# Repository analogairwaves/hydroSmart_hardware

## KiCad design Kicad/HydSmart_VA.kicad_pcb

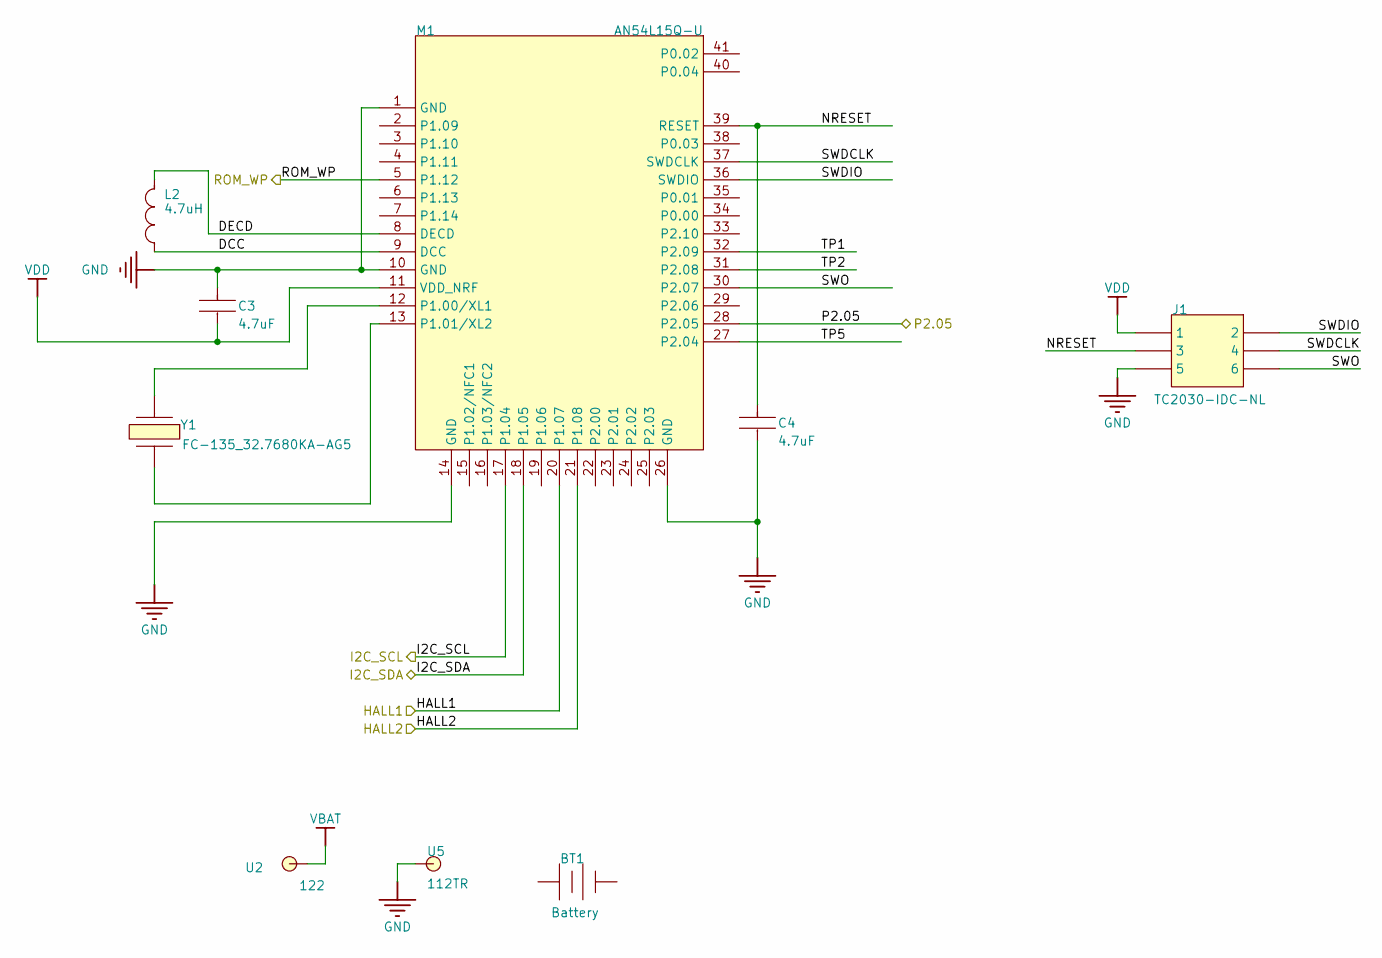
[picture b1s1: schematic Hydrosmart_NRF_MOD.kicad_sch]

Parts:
BT1: Battery; BAT-2; MANUFACTURER_PART_NUMBER CR2477
C3: 4.7uF; C0402; VOLTAGE RATING 16V; MANUFACTURER_PART_NUMBER GRM155D81C475ME15J
C4: 4.7uF; C0402; VOLTAGE RATING 16V; TOLERANCE 20%; MANUFACTURER_PART_NUMBER GRM155D81C475ME15J
J1: TC2030-IDC-NL
L2: 4.7uH; FP-MLZ1608-IPC_A; CURRENT RATING 350mA; TOLERANCE 20%; MANUFACTURER_PART_NUMBER MLZ1608E4R7MT000
M1: AN54L15Q-U; MANUFACTURER_PART_NUMBER AN54L15Q-U
U2: 122; MANUFACTURER_PART_NUMBER 122
U5: 112TR; MANUFACTURER_PART_NUMBER 112TR
Y1: FC-135_32.7680KA-AG5; FC135327680KAAG5; MANUFACTURER_PART_NUMBER FC-135 32.7680KA-AG5; MOUSER PART NUMBER 732-532.7680KA-AG5

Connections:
/HALL1: M1.20 (P1.07); also elsewhere on the board
/HALL2: M1.21 (P1.08); also elsewhere on the board
/Hydrosmart_NRF_MOD/DCC: L2.2, M1.9 (DCC)
/Hydrosmart_NRF_MOD/DECD: L2.1, M1.8 (DECD)
/Hydrosmart_NRF_MOD/NRESET: C4.1, J1.3, M1.39 (RESET)
/Hydrosmart_NRF_MOD/SWDCLK: J1.4, M1.37 (SWDCLK)
/Hydrosmart_NRF_MOD/SWDIO: J1.2, M1.36 (SWDIO)
/Hydrosmart_NRF_MOD/SWO: J1.6, M1.30 (P2.07)
/Hydrosmart_NRF_MOD/TP1: M1.32 (P2.09)
/Hydrosmart_NRF_MOD/TP2: M1.31 (P2.08)
/Hydrosmart_NRF_MOD/TP5: M1.27 (P2.04)
/I2C_SCL: M1.17 (P1.04); also elsewhere on the board
/I2C_SDA: M1.18 (P1.05); also elsewhere on the board
/P2.05: M1.28 (P2.05); also elsewhere on the board
/ROM_WP: M1.5 (P1.12); also elsewhere on the board
GND: C3.1, C4.2, J1.5, M1.1 (GND), M1.10 (GND), M1.14 (GND), M1.26 (GND), U5.1; also elsewhere on the board
unnamed: M1.12 (P1.00/XL1), Y1.1
unnamed: M1.13 (P1.01/XL2), Y1.2 (CRYSTAL_2)
VBAT: U2.1; also elsewhere on the board
VDD: C3.2, J1.1, M1.11 (VDD_NRF); also elsewhere on the board

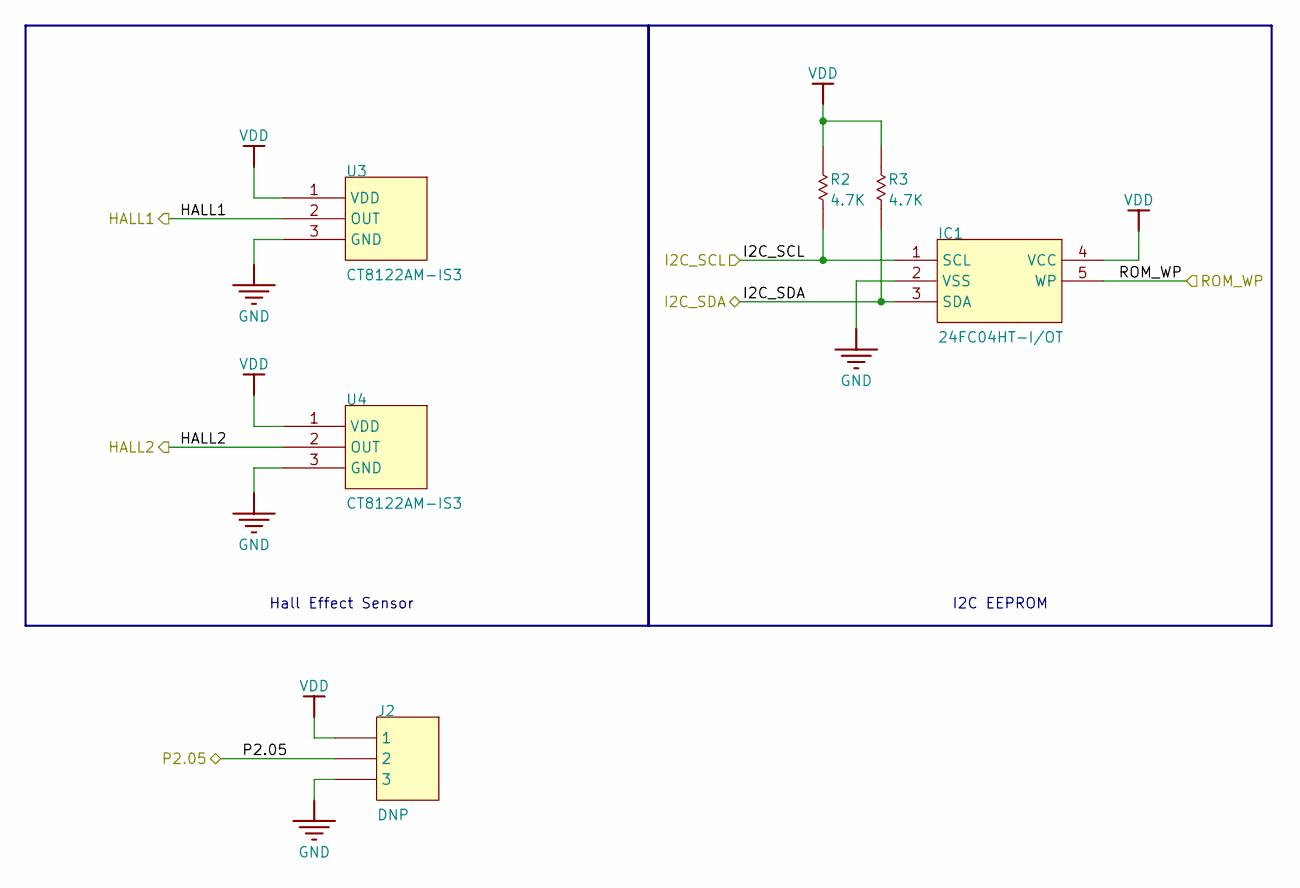
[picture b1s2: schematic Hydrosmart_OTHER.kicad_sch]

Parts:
IC1: 24FC04HT-I/OT; SOT23-5; MANUFACTURER_PART_NUMBER 24FC04HT-I/OT; DIGIKEY PART NUMBER 24FC04HT-I/OTCT-ND
J2: DNP; HDR1X3
R2, R3: 4.7K; R0402; MANUFACTURER_PART_NUMBER ERJ-2RKF4701X
U3, U4: CT8122AM-IS3; SOT95P280X135-3L; MANUFACTURER_PART_NUMBER CT8122AM-IS3

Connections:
/HALL1: U3.2 (OUT); also elsewhere on the board
/HALL2: U4.2 (OUT); also elsewhere on the board
/I2C_SCL: IC1.1 (SCL), R2.1; also elsewhere on the board
/I2C_SDA: IC1.3 (SDA), R3.1; also elsewhere on the board
/P2.05: J2.2; also elsewhere on the board
/ROM_WP: IC1.5 (WP); also elsewhere on the board
GND: IC1.2 (VSS), J2.3, U3.3 (GND), U4.3 (GND); also elsewhere on the board
VDD: IC1.4 (VCC), J2.1, R2.2, R3.2, U3.1 (VDD), U4.1 (VDD); also elsewhere on the board

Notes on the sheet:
I2C EEPROM
Hall Effect Sensor

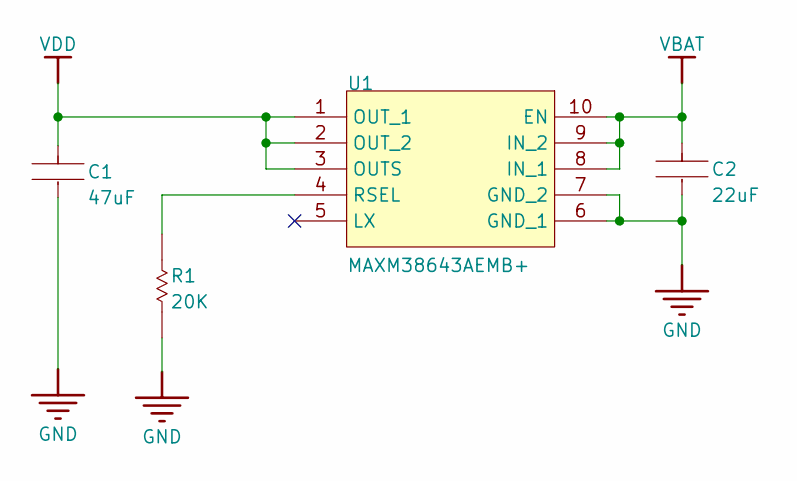
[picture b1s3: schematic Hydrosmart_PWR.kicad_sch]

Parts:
C1: 47uF; FP-C2012-125-0_2-MFG; TOLERANCE 20%; VOLTAGE RATING 6.3V; MANUFACTURER_PART_NUMBER JMK212BBJ476MG-T
C2: 22uF; FP-GRM158-0_2-MFG; MANUFACTURER_PART_NUMBER GRM158R60J226ME01D
R1: 20K; R0402; MANUFACTURER_PART_NUMBER ERJ-2RKF2002X
U1: MAXM38643AEMB+; MAXM38643AEMB; MANUFACTURER_PART_NUMBER MAXM38643AEMB+; MOUSER PART NUMBER 700-MAXM38643AEMB+

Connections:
GND: C1.2, C2.2, R1.1, U1.6 (GND_1), U1.7 (GND_2); also elsewhere on the board
unnamed: R1.2, U1.4 (RSEL)
VBAT: C2.1, U1.8 (IN_1), U1.9 (IN_2), U1.10 (EN); also elsewhere on the board
VDD: C1.1, U1.1 (OUT_1), U1.2 (OUT_2), U1.3 (OUTS); also elsewhere on the board

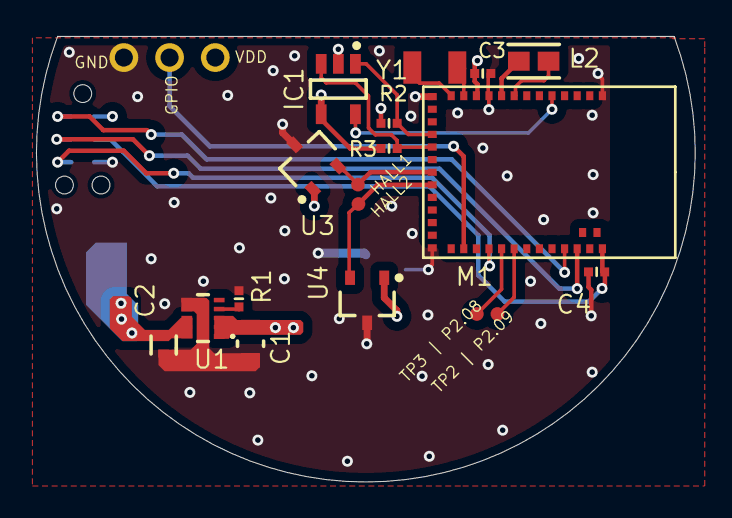
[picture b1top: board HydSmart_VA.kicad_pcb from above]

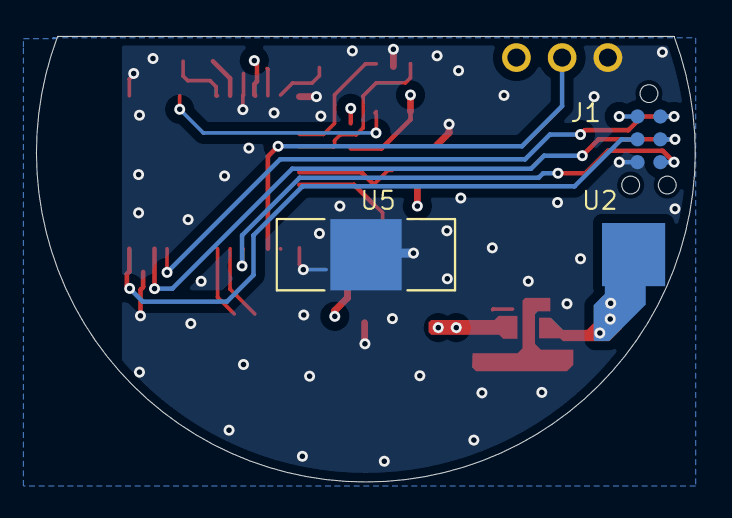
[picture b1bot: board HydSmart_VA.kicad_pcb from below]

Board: 4 copper layers, 36.6 x 24.8 mm, 18 parts (3 on the bottom side), 18 nets.

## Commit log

2025-06-27 VA released initial commit
2025-06-27 Checked, updated design
    + Checked, updated information related to BOM.
    + Updated PCB.
    + Generated manufacturing files.
2025-06-30 + Updated design based on new notes
2025-06-30 + Added 3D model
2025-07-01 - Updated information related to BOM
2025-07-02 + Updated design based on new notes, generated manufacturing files and 3D model
2025-07-02 + Fixed 3D model, moved U2 label
2025-07-02 + Updated schematic
2025-07-02 + Added pull up resistors for I2C signals
2025-07-02 + Moved programming pads to back side
2025-07-09 assembly diagrams added
2025-07-13 + Fixed issue on U2 and U5, added battery to the schematic and BOM
2025-07-23 assembly pictures added
2025-09-03 + Converted design to Kicad, exported 3D model
2025-09-04 + Created library and added information related to BOM: MANUFACTURER and MANUFACTURER PN
2025-09-12 VB changes start. Updated regulator and added test points
